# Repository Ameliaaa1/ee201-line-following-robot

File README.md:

# EE201 Line Following Robot

A line-following robot built using Arduino, a custom sensor array, and PID control. This project was developed for EE 201 and focuses on integrating hardware design, embedded systems, and real-time control.

## Overview

This robot detects and follows a black line on a white surface using a photoresistor sensor array. Sensor readings are processed by an Arduino Mega, which adjusts motor speeds using a PID control algorithm to maintain alignment with the track.

## Features

- Arduino Mega + Adafruit Motor Shield
- 7-photoresistor sensor array with LED illumination
- Custom PCB design
- 3D-printed chassis
- Real-time PID control for line tracking
- Adjustable parameters using potentiometers

## Repository Structure

```text
/firmware/
  /arduino/
    /line_follower_pid/
      line_follower_pid.ino

/hardware/
  /pcb/
    sensor_array.kicad_pcb
    pcb-layout.pdf
    schematic.pdf
  /cad/
    chassis_main.stl
    arduino_breadboard_mount.stl
    prototype_part.stl

/docs/
  final-report.pdf

.gitignore
README.md
```
## Hardware Components

- Arduino Mega
- Adafruit Motor Shield
- DC motors and wheels
- Photoresistors
- LEDs
- Potentiometers
- Custom PCB
- 3D-printed chassis
- Battery power supply

## How It Works

1. Sensors detect light intensity differences between black and white surfaces.
2. The Arduino reads analog values from the sensor array.
3. A PID controller calculates the error relative to the line position.
4. Motor speeds are adjusted dynamically to correct the robot's direction.

## Results

The robot was able to follow the track with stable performance, especially at lower speeds. Environmental light and sensor distance significantly affected accuracy, which was mitigated using LEDs and a light shield.

## Future Improvements

- Improve chassis balance and structural rigidity
- Optimize PCB size and sensor placement
- Enhance performance on sharp turns
- Improve power stability

## Team Members

- Alexa Nassar
- Amelia Cai
- David Wang

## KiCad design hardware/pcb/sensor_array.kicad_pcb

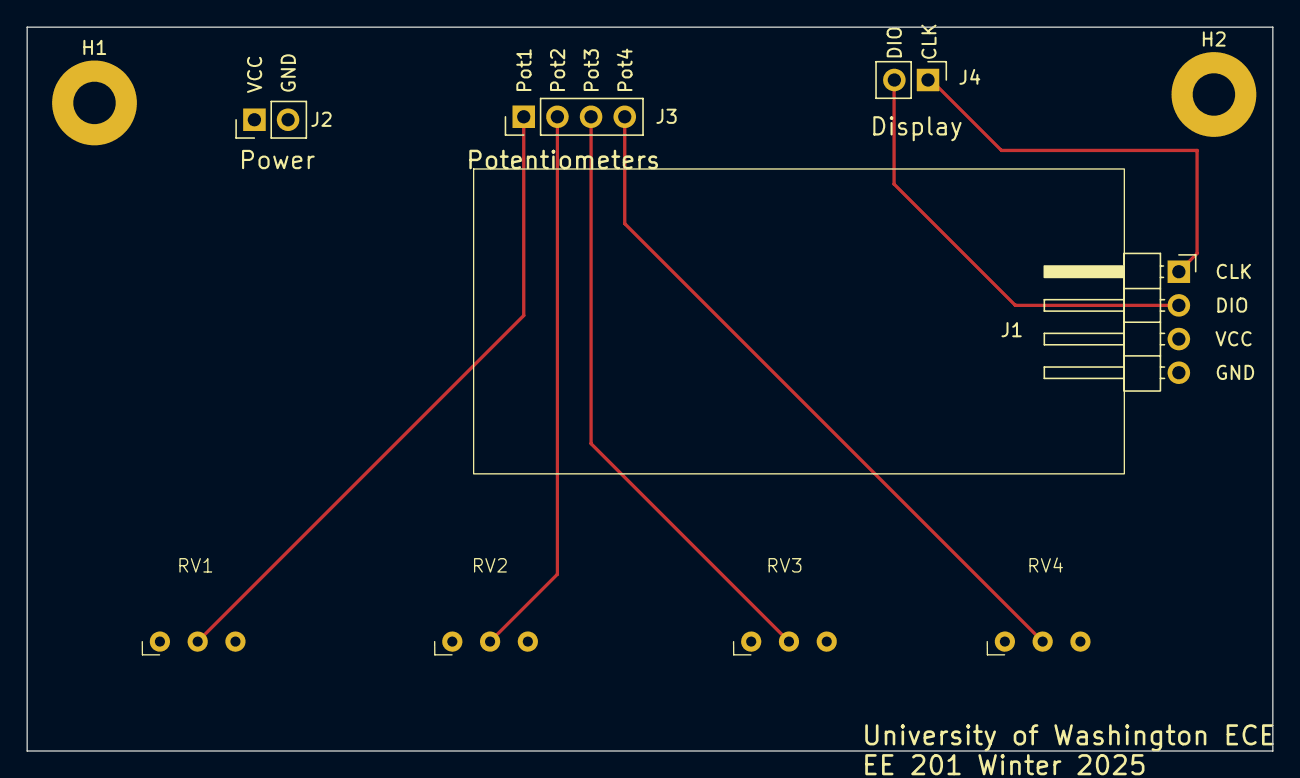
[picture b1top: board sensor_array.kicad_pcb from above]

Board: 2 copper layers, 94.0 x 54.6 mm, 10 parts (0 on the bottom side), 8 nets.

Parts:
H1, H2: MountingHole_Pad; MountingHole_3.2mm_M3_Pad
J1: Display Connection; PinHeader_1x04_P2.54mm_Horizontal_left
J2: Conn_01x02_Pin; PinHeader_1x02_P2.54mm_Vertical
J3: Conn_01x04_Pin; PinHeader_1x04_P2.54mm_Vertical
J4: Arduino Connection; PinHeader_1x02_P2.54mm_Vertical
RV1, RV2, RV3, RV4: R_Potentiometer; Untitled

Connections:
/CLK: J1.1, J4.1
/DIO: J1.2, J4.2
/Pot1: J3.1, RV1.2
/Pot2: J3.2, RV2.2
/Pot3: J3.3, RV3.2
/Pot4: J3.4, RV4.2
GND: H1.1, H2.1, J1.4, J2.2, RV1.3, RV2.3, RV3.3, RV4.3
VCC: J1.3, J2.1, RV1.1, RV2.1, RV3.1, RV4.1

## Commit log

2026-04-06 Add .gitignore
2026-04-06 Add project README
2026-04-06 Revise repository structure in README
    Updated repository structure section to reflect new organization of files and directories.
2026-04-06 Add Arduino firmware
2026-04-06 Add final project report
2026-04-06 Add PCB design file
2026-04-06 Add PCB layout PDF
2026-04-06 Add image and enhance project description in README
